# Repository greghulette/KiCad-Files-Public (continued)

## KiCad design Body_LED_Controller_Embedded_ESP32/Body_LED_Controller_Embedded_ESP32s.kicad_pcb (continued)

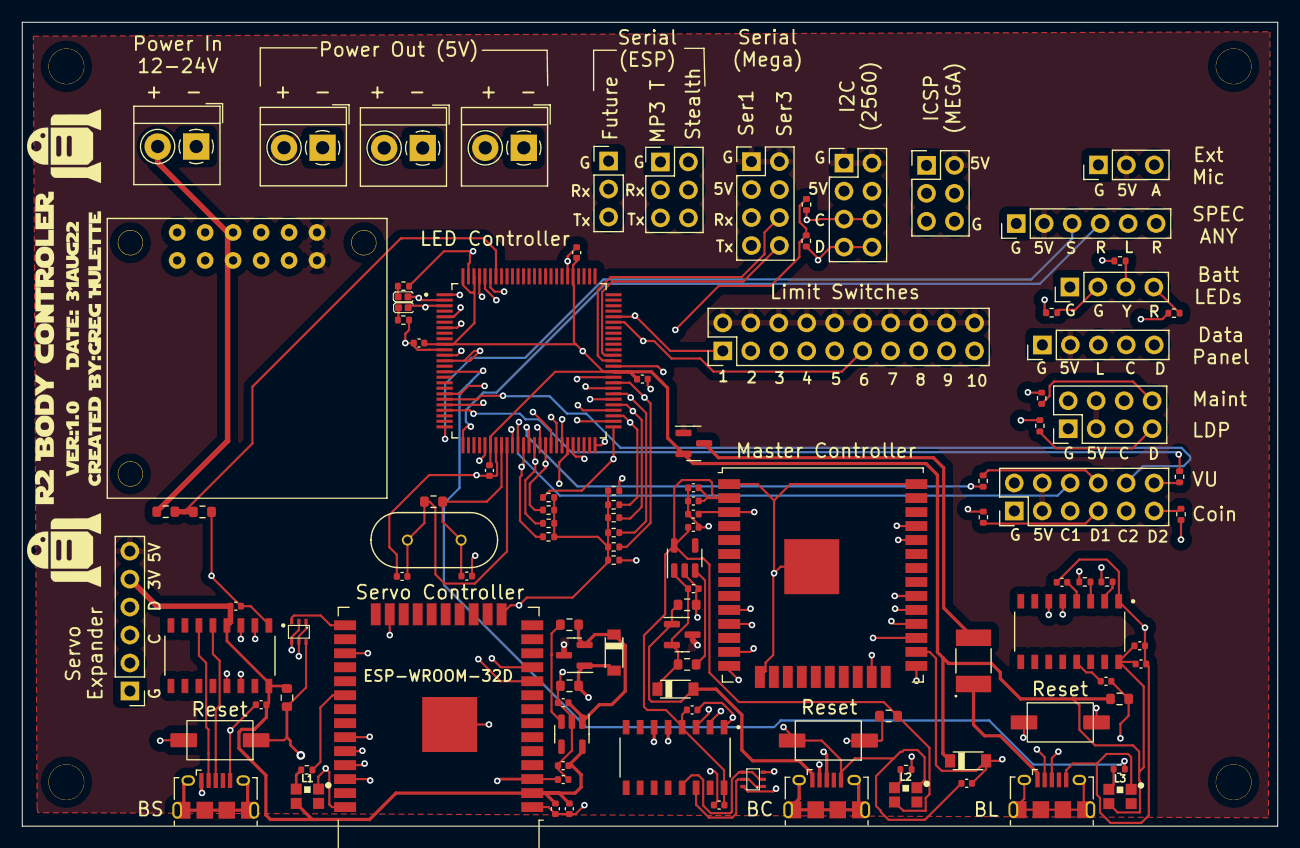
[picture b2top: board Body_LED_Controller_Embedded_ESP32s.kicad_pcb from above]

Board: 4 copper layers, 114.0 x 73.0 mm, 110 parts (0 on the bottom side), 109 nets.

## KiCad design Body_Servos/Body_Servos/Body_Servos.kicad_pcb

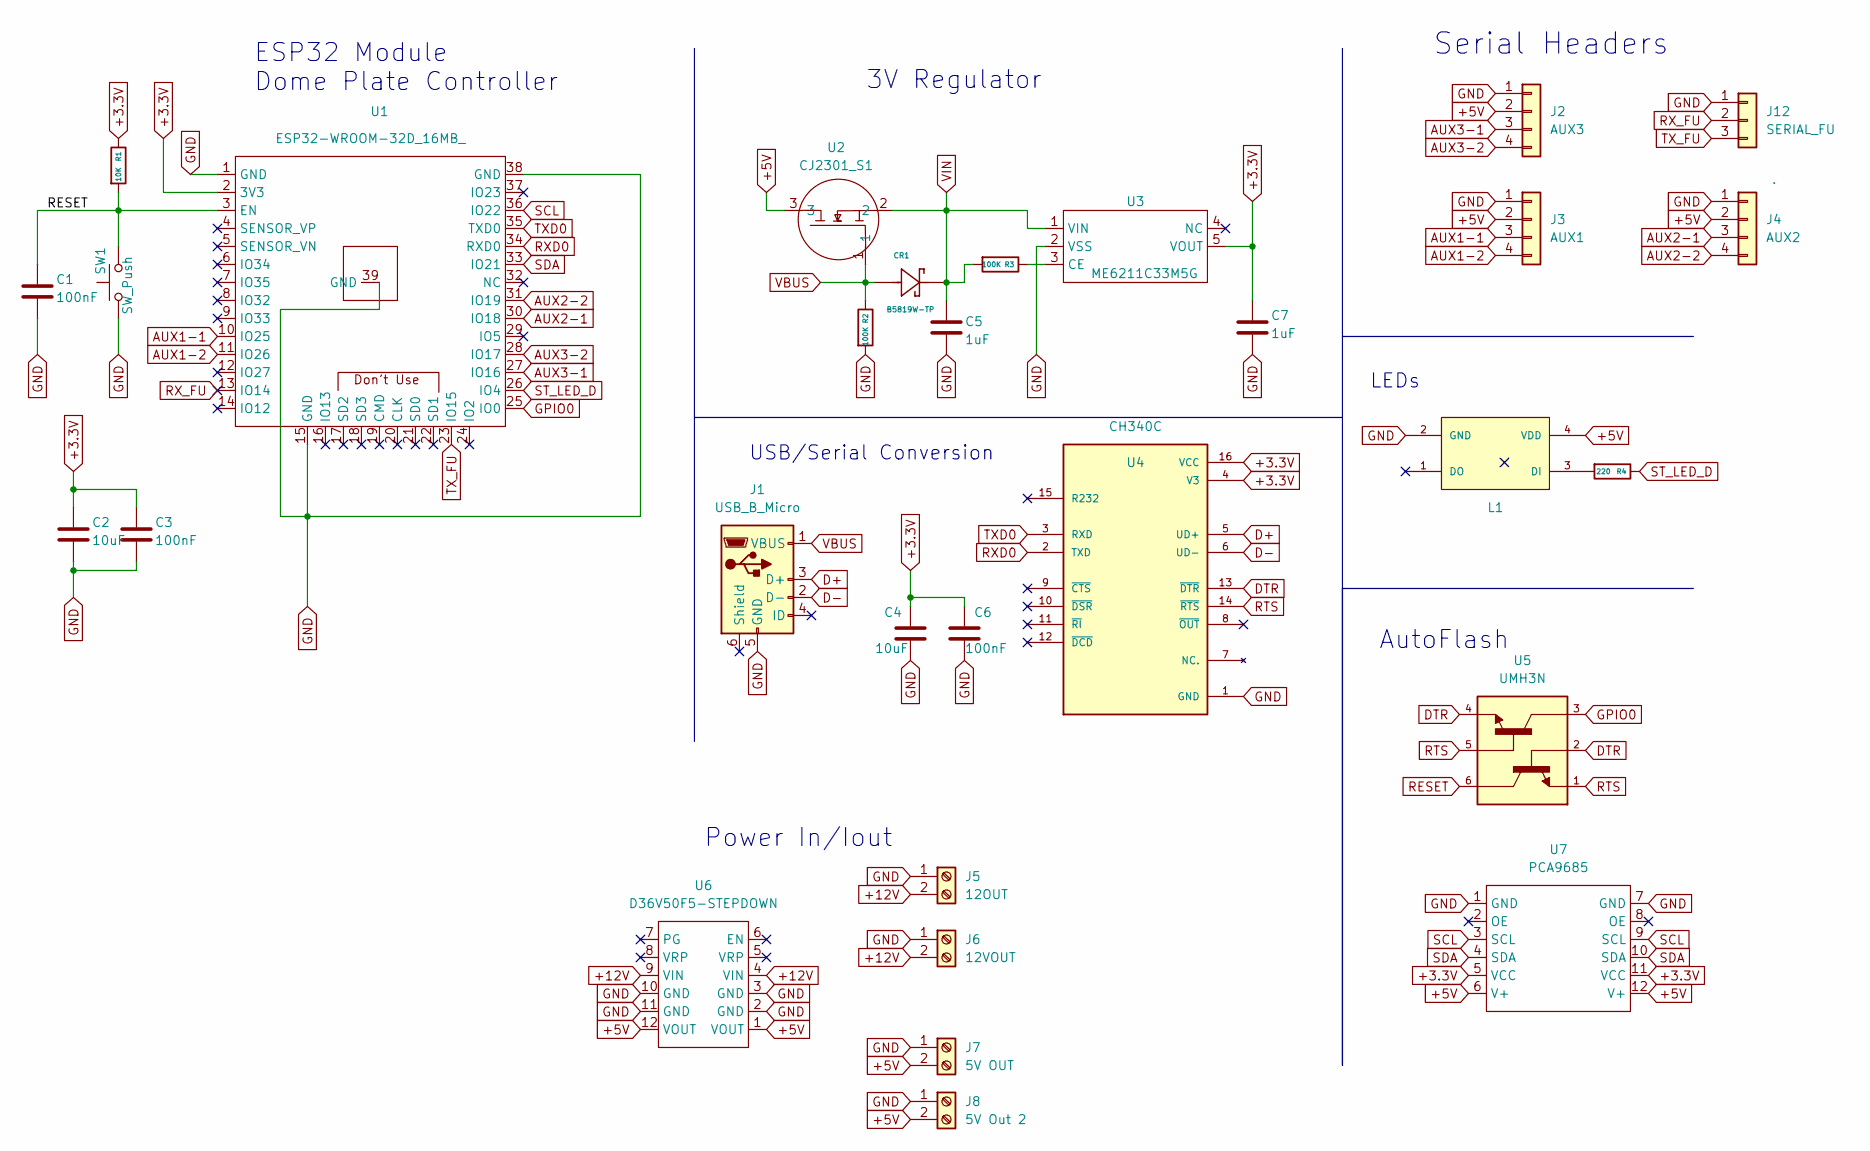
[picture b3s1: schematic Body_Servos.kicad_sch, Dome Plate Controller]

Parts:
C1, C3, C6: 100nF; C_0402_1005Metric; LCSC C307331
C2, C4: 10uF; C_0402_1005Metric; LCSC C315248
C5, C7: 1uF; C_0402_1005Metric; LCSC C77009
CR1: B5819W-TP; SOD3716X135N; LCSC C84354
J1: USB_B_Micro; USB_Micro-B_Amphenol_10118194_Horizontal; LCSC C132563
J2: AUX3; Molex_KK-254_AE-6410-04A_1x04_P2.54mm_Vertical; LCSC C240840
J3: AUX1; Molex_KK-254_AE-6410-04A_1x04_P2.54mm_Vertical; LCSC C240840
J4: AUX2; Molex_KK-254_AE-6410-04A_1x04_P2.54mm_Vertical; LCSC C240840
J5: 12OUT; TerminalBlock_4Ucon_1x02_P3.50mm_Horizontal; LCSC C474892
J6: 12VOUT; TerminalBlock_4Ucon_1x02_P3.50mm_Horizontal; LCSC C474892
J7: 5V OUT; TerminalBlock_4Ucon_1x02_P3.50mm_Horizontal; LCSC C474892
J8: 5V Out 2; TerminalBlock_4Ucon_1x02_P3.50mm_Horizontal; LCSC C474892
J12: SERIAL_FU; Molex_KK-254_AE-6410-03A_1x03_P2.54mm_Vertical; LCSC C471416
L1: WS2812B-2020; LCSC C965555
R1: 10K; R_0603_1608Metric; LCSC C269701
R2, R3: 100K; R_0603_1608Metric; LCSC C25803
R4: 220; R_0402_1005Metric; LCSC C25091
SW1: SW_Push; TS-1101S-B-B-B-W-A; LCSC C692465
U1: ESP32-WROOM-32D_16MB_; ESP32-WROOM-32; LCSC C529578
U2: CJ2301_S1; SOT-23; LCSC C8547
U3: ME6211C33M5G; SOT-23-5; LCSC C82942
U4: CH340C; SOIC127P600X180-16N; PARTREV 2G; LCSC C84681
U5: UMH3N; UMT6; LCSC C62892
U6: D36V50F5-STEPDOWN
U7: PCA9685

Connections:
+3.3V: C2.1, C3.1, C4.1, C6.1, C7.1, R1.1, U1.2 (3V3), U3.5 (VOUT), U4.4 (V3), U4.16 (VCC), U7.5 (VCC), U7.11 (VCC)
+5V: J2.2, J3.2, J4.2, J7.2, J8.2, L1.4 (VDD), U2.3, U6.1 (VOUT), U6.12 (VOUT), U7.6 (V+), U7.12 (V+)
+12V: J5.2, J6.2, U6.4 (VIN), U6.9 (VIN)
AUX1-1: J3.3, U1.10 (IO25)
AUX1-2: J3.4, U1.11 (IO26)
AUX2-1: J4.3, U1.30 (IO18)
AUX2-2: J4.4, U1.31 (IO19)
AUX3-1: J2.3, U1.27 (IO16)
AUX3-2: J2.4, U1.28 (IO17)
D+: J1.3 (D+), U4.5 (UD+)
D-: J1.2 (D-), U4.6 (UD-)
DTR: U4.13 (~DTR), U5.2, U5.4
GND: C1.2, C2.2, C3.2, C4.2, C5.1, C6.2, C7.2, J1.5 (GND), J2.1, J3.1, J4.1, J5.1, J6.1, J7.1, J8.1, J12.1, L1.2 (VSS), R2.2, SW1.1, U1.1 (GND), U1.15 (GND), U1.38 (GND), U1.39 (GND), U3.2 (VSS), U4.1 (GND), U6.2 (GND), U6.3 (GND), U6.10 (GND), U6.11 (GND), U7.1 (GND), U7.7 (GND)
GPIO0: U1.25 (IO0), U5.3
unnamed: L1.3 (DI), R4.2
unnamed: R3.1, U3.3 (CE)
RESET: C1.1, R1.2, SW1.2, U1.3 (EN), U5.6
RTS: U4.14 (~RTS), U5.1, U5.5
RXD0: U1.34 (RXD0), U4.2 (TXD)
RX_FU: J12.2, U1.13 (IO14)
SCL: U1.36 (IO22), U7.3 (SCL), U7.9 (SCL)
SDA: U1.33 (IO21), U7.4 (SDA), U7.10 (SDA)
ST_LED_D: R4.1, U1.26 (IO4)
TXD0: U1.35 (TXD0), U4.3 (RXD)
TX_FU: J12.3, U1.23 (IO15)
VBUS: CR1.A, J1.1 (VBUS), R2.1, U2.1
VIN: C5.2, CR1.C, R3.2, U2.2, U3.1 (VIN)

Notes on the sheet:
ESP32 Module Dome Plate Controller
3V Regulator
LEDs
Power In/Iout
USB/Serial Conversion
AutoFlash
Serial Headers

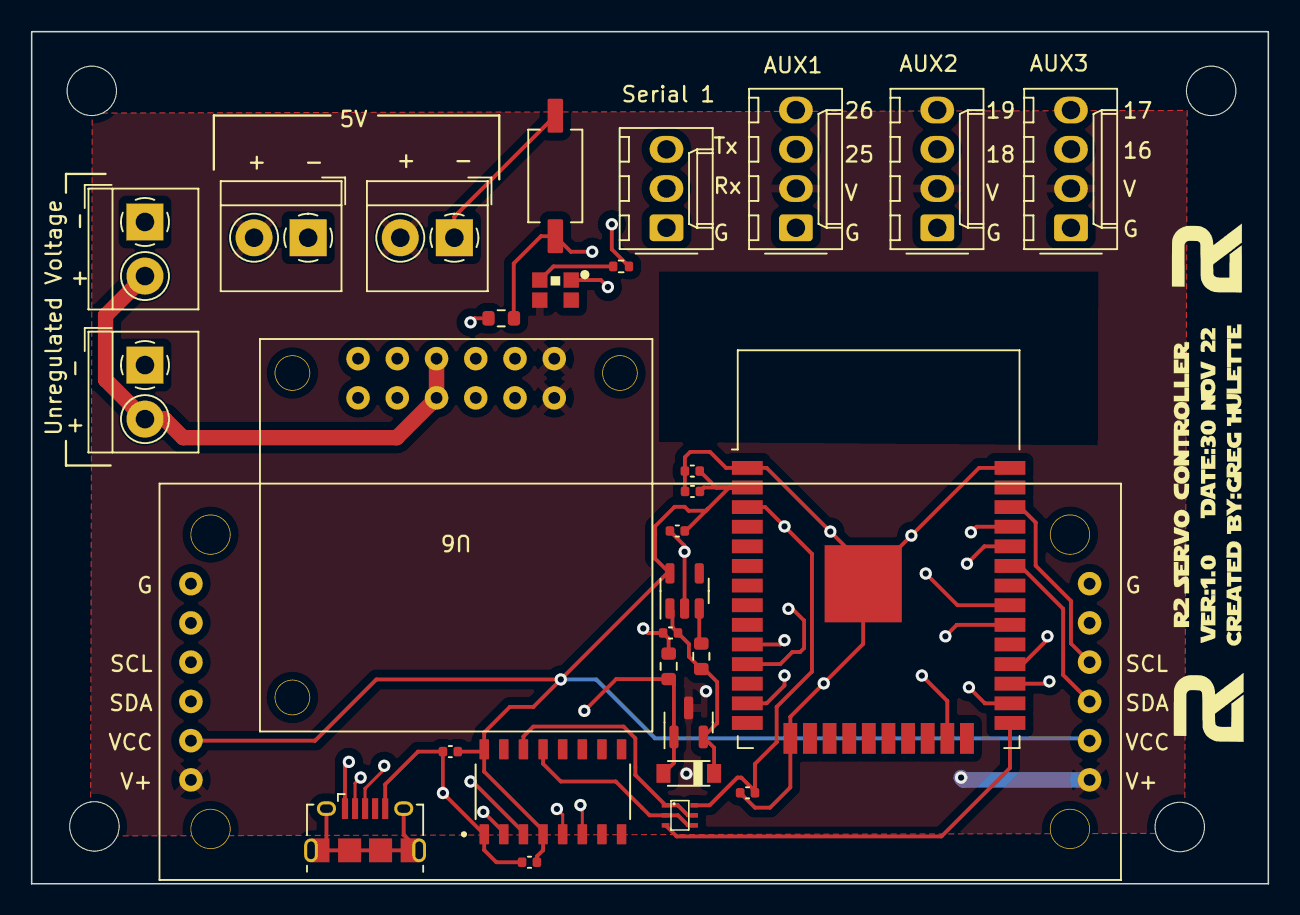
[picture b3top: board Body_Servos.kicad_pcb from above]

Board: 4 copper layers, 80.0 x 55.1 mm, 30 parts (0 on the bottom side), 27 nets.

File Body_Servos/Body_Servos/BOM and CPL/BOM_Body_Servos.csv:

Comment,Designator,Footprint,LCSC
100nF,"C1,C3,C6",Capacitor_SMD:C_0402_1005Metric,C307331
10uF,"C2,C4",Capacitor_SMD:C_0402_1005Metric,C315248
1uF,"C5,C7",Capacitor_SMD:C_0402_1005Metric,C77009
B5819W-TP,CR1,Custom:SOD3716X135N,C84354
USB_B_Micro,J1,Connector_USB:USB_Micro-B_Amphenol_10118194_Horizontal,C132563
SERIAL_FU,J12,Connector_Molex:Molex_KK-254_AE-6410-03A_1x03_P2.54mm_Vertical,C471416
AUX3,J2,Connector_Molex:Molex_KK-254_AE-6410-04A_1x04_P2.54mm_Vertical,C240840 
AUX1,J3,Connector_Molex:Molex_KK-254_AE-6410-04A_1x04_P2.54mm_Vertical,C240840 
AUX2,J4,Connector_Molex:Molex_KK-254_AE-6410-04A_1x04_P2.54mm_Vertical,C240840 
12OUT,J5,TerminalBlock_4Ucon:TerminalBlock_4Ucon_1x02_P3.50mm_Horizontal, C474892
12VOUT,J6,TerminalBlock_4Ucon:TerminalBlock_4Ucon_1x02_P3.50mm_Horizontal, C474892
5V OUT,J7,TerminalBlock_4Ucon:TerminalBlock_4Ucon_1x02_P3.50mm_Horizontal, C474892
5V Out 2,J8,TerminalBlock_4Ucon:TerminalBlock_4Ucon_1x02_P3.50mm_Horizontal, C474892
WS2812B-2020,L1,WS2812B-2020,C965555
10K,R1,Resistor_SMD:R_0603_1608Metric,C269701
100K,"R2,R3",Resistor_SMD:R_0603_1608Metric,C25803
220,R4,Resistor_SMD:R_0402_1005Metric,C25091
SW_Push,SW1,Custom:TS-1101S-B-B-B-W-A, C692465
ESP32-WROOM-32D_16MB_,U1,RF_Module:ESP32-WROOM-32, C529578
CJ2301_S1,U2,Package_TO_SOT_SMD:SOT-23, C8547
ME6211C33M5G,U3,Package_TO_SOT_SMD:SOT-23-5,C82942
CH340C,U4,Custom:SOIC127P600X180-16N,C84681
UMH3N,U5,Custom:UMT6, C62892

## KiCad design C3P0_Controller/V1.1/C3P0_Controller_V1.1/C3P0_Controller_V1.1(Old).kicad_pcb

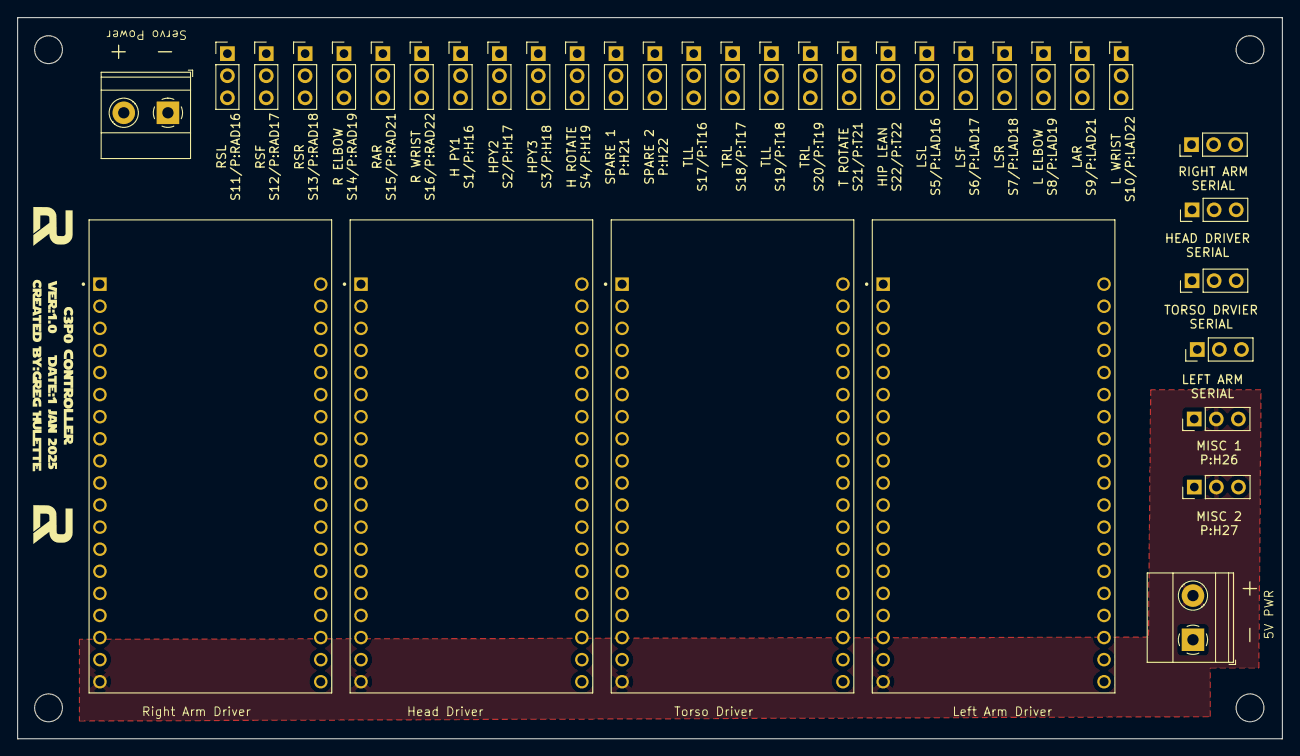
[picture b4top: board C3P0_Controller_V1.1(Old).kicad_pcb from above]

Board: 4 copper layers, 145.5 x 82.9 mm, 36 parts (0 on the bottom side), 37 nets.

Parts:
J1: Servo 1; PinHeader_1x03_P2.54mm_Vertical
J2: Servo 2; PinHeader_1x03_P2.54mm_Vertical
J3: Servo 3; PinHeader_1x03_P2.54mm_Vertical
J4: Servo 4; PinHeader_1x03_P2.54mm_Vertical
J5: Servo 5; PinHeader_1x03_P2.54mm_Vertical
J6: Servo 6; PinHeader_1x03_P2.54mm_Vertical
J7: Servo 7; PinHeader_1x03_P2.54mm_Vertical
J8: Servo 8; PinHeader_1x03_P2.54mm_Vertical
J9: Servo 9; PinHeader_1x03_P2.54mm_Vertical
J10: Servo 10; PinHeader_1x03_P2.54mm_Vertical
J11: Servo 11; PinHeader_1x03_P2.54mm_Vertical
J12: Servo 12; PinHeader_1x03_P2.54mm_Vertical
J13: Servo 13; PinHeader_1x03_P2.54mm_Vertical
J14: Servo 14; PinHeader_1x03_P2.54mm_Vertical
J15: Servo 15; PinHeader_1x03_P2.54mm_Vertical
J16: Servo 16; PinHeader_1x03_P2.54mm_Vertical
J17: Servo 17; PinHeader_1x03_P2.54mm_Vertical
J18: Servo 18; PinHeader_1x03_P2.54mm_Vertical
J19: Servo 19; PinHeader_1x03_P2.54mm_Vertical
J20: Servo 20; PinHeader_1x03_P2.54mm_Vertical
J21: Servo 21; PinHeader_1x03_P2.54mm_Vertical
J22: Servo 22; PinHeader_1x03_P2.54mm_Vertical
J23: Spare Servo 1; PinHeader_1x03_P2.54mm_Vertical
J24: SPARE Servo 1; PinHeader_1x03_P2.54mm_Vertical
J25: Misc 1; PinHeader_1x03_P2.54mm_Vertical
J26: Misc 2; PinHeader_1x03_P2.54mm_Vertical
J30: Head Serial; PinHeader_1x03_P2.54mm_Vertical
J31: Left Arm Serial; PinHeader_1x03_P2.54mm_Vertical
J32: Right Arm Serial; PinHeader_1x03_P2.54mm_Vertical
J33: Torso Serial; PinHeader_1x03_P2.54mm_Vertical
J50: Servo Power Input; TerminalBlock_Phoenix_MKDS-1,5-2-5.08_1x02_P5.08mm_Horizont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
J51: 5V Input; TerminalBlock_Phoenix_MKDS-1,5-2-5.08_1x02_P5.08mm_Horizont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
U1: Right Arm Driver; MODULE_ESP32-DEVKITC-32D
U2: Head Driver; MODULE_ESP32-DEVKITC-32D
U3: Torso Driver; MODULE_ESP32-DEVKITC-32D
U4: Left Arm Driver; MODULE_ESP32-DEVKITC-32D

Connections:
5V: J25.2, J26.2, J51.2, U1.J2-19 (EXT_5V), U2.J2-19 (EXT_5V), U3.J2-19 (EXT_5V), U4.J2-19 (EXT_5V)
GND: J1.1, J2.1, J3.1, J4.1, J5.1, J6.1, J7.1, J8.1, J9.1, J10.1, J11.1, J12.1, J13.1, J14.1, J15.1, J16.1, J17.1, J18.1, J19.1, J20.1, J21.1, J22.1, J23.1, J24.1, J25.1, J26.1, J30.1, J31.1, J32.1, J33.1, J50.1, J51.1, U1.J3-1 (GND3), U2.J3-1 (GND3), U3.J3-1 (GND3), U4.J3-1 (GND3)
H_RX: J30.2, U2.J3-5 (RXD0)
H_TX: J30.3, U2.J3-4 (TXD0)
LA_RX: J31.2, U4.J3-5 (RXD0)
LA_TX: J31.3, U4.J3-4 (TXD0)
MISC_1: J25.3, U2.J2-10 (IO26)
MISC_2: J26.3, U2.J2-11 (IO27)
RA_RX: J32.2, U1.J3-5 (RXD0)
RA_TX: J32.3, U1.J3-4 (TXD0)
SPR_1: J23.3, U2.J3-6 (IO21)
SPR_2: J24.3, U2.J3-3 (IO22)
SRV_1: J1.3, U2.J3-12 (IO16)
SRV_2: J2.3, U2.J3-11 (IO17)
SRV_3: J3.3, U2.J3-9 (IO18)
SRV_4: J4.3, U2.J3-8 (IO19)
SRV_5: J5.3, U4.J3-12 (IO16)
SRV_6: J6.3, U4.J3-11 (IO17)
SRV_7: J7.3, U4.J3-9 (IO18)
SRV_8: J8.3, U4.J3-8 (IO19)
SRV_9: J9.3, U4.J3-6 (IO21)
SRV_10: J10.3, U4.J3-3 (IO22)
SRV_11: J11.3, U1.J3-12 (IO16)
SRV_12: J12.3, U1.J3-11 (IO17)
SRV_13: J13.3, U1.J3-9 (IO18)
SRV_14: J14.3, U1.J3-8 (IO19)
SRV_15: J15.3, U1.J3-6 (IO21)
SRV_16: J16.3, U1.J3-3 (IO22)
SRV_17: J17.3, U3.J3-12 (IO16)
SRV_18: J18.3, U3.J3-11 (IO17)
SRV_19: J19.3, U3.J3-9 (IO18)
SRV_20: J20.3, U3.J3-8 (IO19)
SRV_21: J21.3, U3.J3-6 (IO21)
SRV_22: J22.3, U3.J3-3 (IO22)
SVR_PWR: J1.2, J2.2, J3.2, J4.2, J5.2, J6.2, J7.2, J8.2, J9.2, J10.2, J11.2, J12.2, J13.2, J14.2, J15.2, J16.2, J17.2, J18.2, J19.2, J20.2, J21.2, J22.2, J23.2, J24.2, J50.2
T_RX: J33.2, U3.J3-5 (RXD0)
T_TX: J33.3, U3.J3-4 (TXD0)
